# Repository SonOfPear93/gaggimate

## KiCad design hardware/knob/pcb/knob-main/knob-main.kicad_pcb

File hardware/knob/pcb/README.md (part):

## Board A — knob-base

Status: rev 1 layout, generated 2026-11-07 while Ryan was away. ERC/DRC clean, not yet ordered.
Decisions marked **[Claude's call]** are open to change.

Files (`knob-base/`): `knob-base.kicad_sch`, `knob-base.kicad_pcb`, `knob-base.kicad_pro`,
`lib/knob-base.pretty` (SmartKnob hole footprints), `scripts/` (generators), `fab/` (outputs).
The design is fully script-generated; edit the scripts, not the board, or regeneration will undo it:

```sh
PY=/Applications/KiCad/KiCad.app/Contents/Frameworks/Python.framework/Versions/3.9/bin/python3
cd hardware/knob/pcb/knob-base
python3 scripts/gen_sch.py      # schematic
$PY scripts/gen_pcb.py          # placement, hand routes on the flexure, grid router, GND pours (~20 s)
$PY scripts/gen_fab.py          # Gerbers/drill zip, JLC BOM + CPL, renders, schematic PDF, ERC/DRC reports
```

### Credit and what changed from SmartKnob

Derived from **SmartKnob View `electronics/view_base` by Scott Bezek (Apache-2.0)**,
https://github.com/scottbez1/smartknob. Kept, at the same coordinates: the press-sensor flexure
(all inner Edge.Cuts: arc slots r = 15–16 mm, 1.0 mm radial slots either side of four 5 mm arms out to
r = 23.8 mm, the motor-wire cut-out and the Ø3 display-wire hole), MT6701 (U1) at the exact centre on
the front, its 100 n (C20), the four 2512 strain-gauge resistors (R18–R21) on the back of the ±X arms,
the HX711 circuit (U4 + PNP AVDD regulator Q1/R3/R4, excitation filter, 100 Ω/100 n input filter,
decoupling, GNDA–GND net tie NT1), motor holes H1–H3, M2 holes H4–H7 and alignment holes H8/H9.
Hole footprints are copied from SmartKnob's `lib/Holes.pretty`; reference designators match view_base.

Removed: ESP32 module, USB-C, CH340, both regulators, TMC6300, SK6812 LEDs, VEML7700, LCD pads,
test points and the J4/J5 glued-gauge pads. Changed:
- Outline: 81.2 mm rounded square → **Ø75.0 mm circle**, 1.2 mm FR4, 2 layers.
- HX711 group moved onto the rigid quadrant at 135° (back side); power is 3V3 from Board B.
- **[Claude's call]** L1 3.3 µH (C307744, extended, 5k stock) → FB1 ferrite bead GZ2012D101TF (C1015, basic).
  Same 0805 footprint, so C307744 can be fitted instead if the HX711 reading is noisier than SmartKnob's.
- **[Claude's call]** MMBT4403 → SS8550 (C8542, basic; same SOT-23 B-E-C pinout; the HX711 datasheet's own PNP).
- Bridge routing keeps SmartKnob's topology (+X-arm nets cross the inner disc and leave up the 90° arm,
  −X-arm nets leave along the −X arm) but is redrawn for 0.25 mm tracks / 0.15 mm clearance / 0.3 mm edge
  clearance. R18's E+ leaves from the outer root and goes round on the ring. The encoder bus (3V3, CS,
  CLK, DO on F.Cu; GND on B.Cu) now runs down the 270° arm instead of the −X arm.
- Added J1 (JST-SH 8p) and the 3.0 × 7.0 mm wire slot.

### Placement and coordinates

Front view (looking at the knob side), origin at the board centre, +x right, +y up, mm, angles CCW from +x
(alignment holes on the x axis). KiCad file coordinates: board centre at (100, 100), KiCad X = 100 + x,
KiCad Y = 100 − y.

| Item | Position (x, y) | Notes |
|---|---|---|
| Board outline | circle Ø75.0 | 1.2 mm thick |
| U1 MT6701CT (front) | (0, 0) | under the motor magnet, as SmartKnob |
| H1 / H2 / H3 motor (M1.6) | (5.125, −8.877), (−10.25, 0), (5.125, 8.877) | r = 10.25 at −60°/180°/60°, Ø1.7 plated, pad Ø2.4 |
| H4 / H5 / H6 / H7 mount (M2) | (0, −29.8), (−29.8, 0), (0, 29.8), (29.8, 0) | r = 29.8 at 270°/180°/90°/0°, Ø2.2 plated, pad Ø3.5 |
| H8 / H9 alignment | (35, 0), (−35, 0) | r = 35 at 0°/180°, Ø2.2 plated, pad Ø3.5 |
| **Wire slot** | centre (−23.688, −23.688) | r = 33.5 at 225°, 3.0 × 7.0 obround, long axis tangential (along the 135°/315° direction); inner edge r = 32.0, outer r = 35.0; ≥ 8 mm outside the flexure slots, ~4.9 mm from J1's courtyard |
| Display-wire hole (kept) | (−7.071, −7.071) | Ø3.0, r = 10 at 225° |
| Motor-wire cut-out (kept) | centre (8.75, 0) | 3.5 × 7.0, r = 0.75 corners |
| Strain gauges R18/R19/R20/R21 (back) | (23.5, 0), (15.6, 0), (−15.6, 0), (−23.5, 0) | 2512 across the arm roots |
| U4 HX711 (back) | (−15.91, 15.91) | r = 22.5 at 135°, rotated 45°; passives at r ≈ 17–32 |
| **J1 JST-SH (back)** | footprint origin (−10.0, −29.5) | pins 1…8 at y = −31.5, x = −13.5 … −6.5 (front view); cable opening faces the board centre (+y) |

Max part height on the back (towards Board B): J1 2.9 mm (plus the mated plug in front of the opening),
U4 1.75 mm, everything else ≤ 1.3 mm. Front side: only U1 (1.75 mm) and C20, within r ≈ 5 of the centre.

**[Claude's call]** The brief said "HX711 on the rigid ring r ≈ 29–37". The ring between the M2 holes and the
edge is ~7 mm wide and already holds H4–H9, so U4 and its 12 passives sit on the quadrant between the 90° and
180° arms at r ≈ 17–32. That area is rigid: the radial flexure slots stop at r = 23.8, so each quadrant is joined to
the outer ring along its full width (SmartKnob put LEDs and caps there).

### Connector J1 to Board B

JST SM08B-SRSS-TB (side entry, 1.0 mm), back side. Board B uses the same header (C160407), so the cable is a
JST-SH 8-way **pin-1-to-pin-1** (same-side) lead, e.g. two SHR-08V-S housings with SSH crimps or a pre-made
"Qwiic-style" 8-way cable.

| Pin | Net | Board A use |
|---|---|---|
| 1 | 3V3 | MT6701 VDD/MODE, HX711 VSUP/DVDD/RATE, PNP emitter |
| 2 | GND | |
| 3 | ENC_CS | MT6701 pin 8 (CSN) |
| 4 | ENC_CLK | MT6701 pin 7 (CLK) |
| 5 | ENC_DO | MT6701 pin 6 (DO) |
| 6 | HX_SCK | HX711 PD_SCK |
| 7 | HX_DOUT | HX711 DOUT |
| 8 | GND | |

MT6701 MODE is tied to VDD (SSI, as SmartKnob). HX711 RATE is tied high (80 SPS), XI to AGND (internal
oscillator). Board A has no pull-ups or series resistors on the interface; SmartKnob had 2.2 k pull-ups on the
encoder DO/CLK on its main board, so put those on Board B if the SSI read needs them.

### Parts (JLC, qty 5 boards)

Stock and price from the local kicad-jlcpcb-tools parts DB (snapshot dated 2026-09-21; not refreshed today,
that needs a download). Unit price is the JLC tier for the quantity bought.

| Ref | Value | MPN | LCSC | Type | Stock | Unit | Qty (5 bds) | Cost |
|---|---|---|---|---|---|---|---|---|
| U1 | MT6701CT-STD-R | Novosense MT6701CT-STD-R | C3003196 | Extended | 5,421 | $1.724 | 5 | $8.62 |
| U4 | HX711 | Avia HX711 | C6705483 | Extended | 177,864 | $0.505 | 5 | $2.52 |
| J1 | JST-SH 8p | JST SM08B-SRSS-TB(LF)(SN) | C160407 | Extended | 125,076 | $0.332 | 5 | $1.66 |
| R18–R21 | 330 Ω 2512 (strain) | Uniroyal 25121WJ0331T4E | C19866 | Extended | 113,348 | $0.028 | 20 | $0.56 |
| Q1 | SS8550 | CJ SS8550 Y2 | C8542 | Basic | 888,952 | $0.015 | 5 | $0.07 |
| FB1 | 100 Ω@100 MHz 0805 | Sunlord GZ2012D101TF | C1015 | Basic | 2,395,344 | $0.027 | 5 | $0.14 |
| C16, C18 | 10 µF 0805 | Samsung CL21A106KAYNNNE | C15850 | Basic | 5,982,699 | $0.084 | 10 | $0.84 |
| C12, C19, C20, C22, C23 | 100 nF 0603 | Yageo CC0603KRX7R9BB104 | C14663 | Basic | 53,676,678 | $0.012 | 25 | $0.30 |
| R3 | 10 k 0603 | Uniroyal 0603WAF1002T5E | C25804 | Basic | 24,484,378 | $0.003 | 5 | $0.01 |
| R4 | 8.2 k 0603 | Uniroyal 0603WAF8201T5E | C25981 | Basic | 1,133,039 | $0.004 | 5 | $0.02 |
| R5, R6 | 100 Ω 0603 | Uniroyal 0603WAF1000T5E | C22775 | Basic | 12,954,942 | $0.003 | 10 | $0.03 |
| NT1 | net tie | copper only | — | not placed | | | | |

BOM cost for 5 boards: **components ≈ $14.78**, plus 4 extended-part fees (≈ $3 each) ≈ **$26.80**. Not included:
bare PCBs (Ø75, 1.2 mm, 2 layers), PCBA setup for **both sides** (U1/C20 front, the rest back), stencil, shipping.
No JLC quote was requested. Every line is ≥ 10× the build quantity; the tightest is the MT6701 (5.4k).

### Fab outputs (`knob-base/fab/`)

- `knob-base-gerbers.zip`: Gerbers (F/B Cu, Mask, Paste, Silkscreen, Edge.Cuts) + Excellon drills (PTH; the NPTH file is empty).
- `knob-base-BOM-JLC.csv`, `knob-base-CPL-JLC.csv`: JLC format. CPL rotation uses kicad-jlcpcb-tools' rule (back side
  `180 − rot`) plus its corrections (SOIC +270, SOT-23 −90) and +180 for the JST SH header (by analogy with the
  plugin's JST_GH_SM/JST_PH_S entries; Board B uses the same value).
- `knob-base-top.png`, `knob-base-bottom.png` (`kicad-cli pcb render`), `knob-base-schematic.pdf`, `erc-report.txt`, `drc-report.txt`.
- Order settings: 1.2 mm thickness (the flexure depends on it), 2 layers, any mask colour.

### Verification

```sh
kicad-cli sch erc knob-base.kicad_sch                                     # 0 errors, 0 warnings
kicad-cli pcb drc --schematic-parity --severity-all knob-base.kicad_pcb   # 0 violations, 0 unconnected, 0 parity issues
```

Rules in `knob-base.kicad_pro`: clearance 0.15 mm (pours 0.25), all tracks 0.25 mm, vias 0.6/0.3 mm, copper to edge
0.3 mm, min drill 0.3 mm. Routing: the flexure/arm traces are hand-placed in `gen_pcb.py`; everything outside the
flexure is routed by `scripts/router.py` (a small 2-layer grid maze router, kept away from the arms, the inner disc and
the M2 screw/nut and alignment-pin areas), giving 163 track segments and 28 vias. GND is poured on both layers.

### Risks / open points (Board A)

1. **Board B's 225° mounting hole (r = 33) sits directly under this wire slot (r = 33.5, 225°).** The 16 wires
   will drop onto B's screw/standoff. Move one of them (for example B's hole to 210°/240°, or the slot) before ordering.
   Board B's 135° hole (r = 33) also lands near A's back-side HX711 passives (R5/R6 reach r ≈ 32.5): a standoff there needs
   to be ≤ Ø2 mm wide at A, or the hole moved.
2. Flexure geometry is SmartKnob's, but the clamp ring is now round, and the quadrants carry the HX711 group.
   Press sensitivity and stiffness are untested.
3. Two-sided assembly (U1 and C20 front, everything else back), as SmartKnob's strain gauges were already on the back.
   JLC charges a second side; the economic PCBA service may not cover it.
4. CPL rotations for J1 (+180, guessed), Q1 and the SOICs must be checked in JLC's placement preview.
5. J1 is a side-entry header with its opening facing the centre. The mated plug lies over bare tracks towards
   r ≈ 23 and needs ~5 mm of space in front of the opening plus ~3 mm height. Board B parts below it must clear
   that (A–B gap target 8 mm).
6. Strain signals: S+ and E+ have longer runs than SmartKnob (the HX711 moved further from the +X arm), and some
   of the outer routing uses vias. The 100 Ω/100 nF input filter, separate GNDA (net tie at the HX711) and GND pours
   on both sides should hold the noise down, but this is unproven. FB1 vs the original 3.3 µH is a second variable.
7. The flexure slots are 1.0 mm wide, at JLC's minimum milled-slot width (unchanged from SmartKnob).
8. Parts DB snapshot is ~7 weeks old. Re-check MT6701 (C3003196) stock before ordering.

## Board B — knob-main

Status: rev 1 layout, generated 2026-11-07 while Ryan was away. Not yet ordered. Decisions marked
**[Claude's call]** are open to change. Verification results are in the "Verification" subsection below.

Files (`knob-main/`): `knob-main.kicad_sch/.kicad_pcb/.kicad_pro`, `knob-main.kicad_sym` (local symbol: AP7361C-33ER), `knob-main.pretty/` (local footprints:
ESP32-S3-WROOM-1 copy with 0.3 mm EP vias, 13-pad wire field, motor pads), `gen/` (generators), `fab/` (outputs).
Everything is script-generated; edit the scripts, not the board:

```sh
PY=/Applications/KiCad/KiCad.app/Contents/Frameworks/Python.framework/Versions/3.9/bin/python3
K=/Applications/KiCad/KiCad.app/Contents/MacOS/kicad-cli
cd hardware/knob/pcb/knob-main
python3 gen/make_footprints.py && python3 gen/build_sch.py           # local footprints, schematic + .kicad_pro
$K sch upgrade knob-main.kicad_sch && $K sch export netlist -o /tmp/b.net knob-main.kicad_sch
$PY gen/build_pcb.py /tmp/b.net knob-main.kicad_pcb && python3 gen/build_sch.py --pro-only
$PY gen/prefan.py knob-main.kicad_pcb    # hand routes at the DRV8311 + GND/3V3 fan-out vias to the inner planes
$PY gen/dsn.py knob-main.kicad_pcb /tmp/b.dsn                         # then Freerouting 1.9.0 (Java 21):
java -jar freerouting-1.9.0.jar -de /tmp/b.dsn -do /tmp/b.ses -mp 30 -inc Plane
$PY gen/ses.py knob-main.kicad_pcb /tmp/b.ses                         # 0 unrouted in this revision
$PY gen/finish_pcb.py knob-main.kicad_pcb   # cleanup, pours, stitching vias
$PY gen/fab.py knob-main.kicad_pcb fab      # gerbers/drill zip, JLC BOM/CPL, renders
```

(`gen/inner_route.py` and `dsn.py --in2-signal` exist for finishing leftovers on In2 but were not needed here.
`build_pcb.py` calls `pcbnew.SaveBoard`, which rewrites the .kicad_pro with defaults, hence the
`--pro-only` re-run that restores the net classes. Freerouting 2.x needs Java 25 and routed this board badly;
1.9.0 is used.)

### What is on it

| Block | Parts | Notes |
|---|---|---|
| MCU | U1 ESP32-S3-WROOM-1-N16R8 | GPIO map exactly as the design doc §5 table (no changes). EN: 10k/1µF RC + RESET button SW1. GPIO0: 10k pull-up + BOOT button SW2. Status LED D3 (red) + 1k on GPIO48. 10µF + 100nF at the 3V3 pin. |
| USB | J1 USB-C 16P (HRO TYPE-C-31-M-12), U2 USBLC6-2SC6, R1/R2 5.1k CC pull-downs | D+/D− direct to GPIO20/19, VBUS also clamped by U2. SBU unused. |
| 5 V in | J2 JST-XH B4B-XH-A (THT, **bottom side**), D1/D2 SS34 Schottky OR, C1 22µF | J2 pinout = GaggiMate controller J4 (the display connector): 1 +5V, 2 controller UART_TX0, 3 controller UART_RX0, 4 GND. Only 1/4 are used; 2/3 go to test pads TP6/TP7. +5V after the diodes ≈ 4.5–4.6 V. |
| 3.3 V | U3 AP7361C-33ER-13 (Diodes, SOT-223R, 1 A, 340 mV dropout @ 1 A), C2 10µF/25V in, C3 22µF + C4 100nF out | Datasheet asks CIN ≥ 1 µF, COUT ≥ 2.2 µF ceramic. Tab (= OUT on the "R" pinout) on a top-copper +3V3 island with vias into the In2 +3V3 plane. See the U3 note below. |
| Panel power | Q1 AO3401A high-side P-FET, Q2 2N7002, R14 100k, C8 100nF, R15 10k, R16 100k, C9 10µF | LCD_EN (GPIO17) high = panel on. Gate RC gives ≈1 ms soft start so the panel's input caps don't sag the 3V3 rail. Default off (R16 pull-down). |
| Display/touch | R6–R11 33Ω series on QSPI CS/CLK/D0–D3 (at the ESP32), R12/R13 4.7k touch I2C pull-ups **to 3V3_LCD** | Pull-ups go to the switched rail so nothing back-powers the touch IC when the panel is off. **[Claude's call]** the 33Ω resistors damp ringing on the ~10–15 cm loose wire bundle. |
| Motor | U4 DRV8311HRRWR, J5 Molex PicoBlade 53261-0371, J6 3 bare pads | See "DRV8311H configuration". |
| Board A link | J8 JST-SH SM08B-SRSS-TB, R21–R23 2.2k pull-ups on ENC_CS/ENC_CLK/ENC_DO | Board A has no pull-ups; SmartKnob used 2.2k. |
| Wire pads | J7 13 bare THT pads (2 staggered rows, 2.0 mm pitch, Ø0.9 drill) | Screen bundle, same numbering as board C J2. |
| Test pads | TP1 +5V, TP2 +3V3, TP3 GND, TP4 U0TXD, TP5 U0RXD, TP6/TP7 XH pins 2/3 | Ø1.5 mm SMD pads. |

### DRV8311H configuration (hardware variant)

- **MODE tied to AVDD → 3x PWM mode** (datasheet Table 8-2; this setting also selects the 5 A OCP level).
  INHA/INHB/INHC = GPIO4/GPIO5/GPIO18 PWM. All three INLx are tied together to **DRV_EN (GPIO47, 100k pull-down)**:
  INLx = 0 puts every half-bridge in Hi-Z (Table 8-4), so the motor is free while the ESP32 boots.
- nSLEEP = GPIO21 with 100k pull-down. nFAULT → GPIO3 with 10k pull-up to 3V3.
- **GAIN left open (Hi-Z) → 1 V/A** current-sense gain, ±1.65 A full scale around CSAREF/2. SOA/SOB → GPIO1/GPIO2 (ADC1); SOC unused.
  **[Claude's call]**: the gimbal motor draws well under 1 A at 5 V, so 1 V/A uses the ADC range without clipping.
- **SLEW: 47k to GND → 75 V/µs** (and the matching dead time). **[Claude's call]**: slow enough for low EMI near the
  QSPI bundle, fast enough for 20–30 kHz FOC PWM.
- CSAREF tied to AVDD with 100nF; AVDD 1µF; CP–VM 100nF/50V; VM 100nF/50V + 2× 22µF/25V; VIN_AVDD (from +5V) 100nF + 10µF/25V.
- The exposed pad has 4 × 0.3 mm vias to the In1 GND plane. PGND/AGND pins are tied straight into the pad.

### Placement and coordinates

Front view (looking at the knob; board B's top side faces board A and the front), origin at the board centre,
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
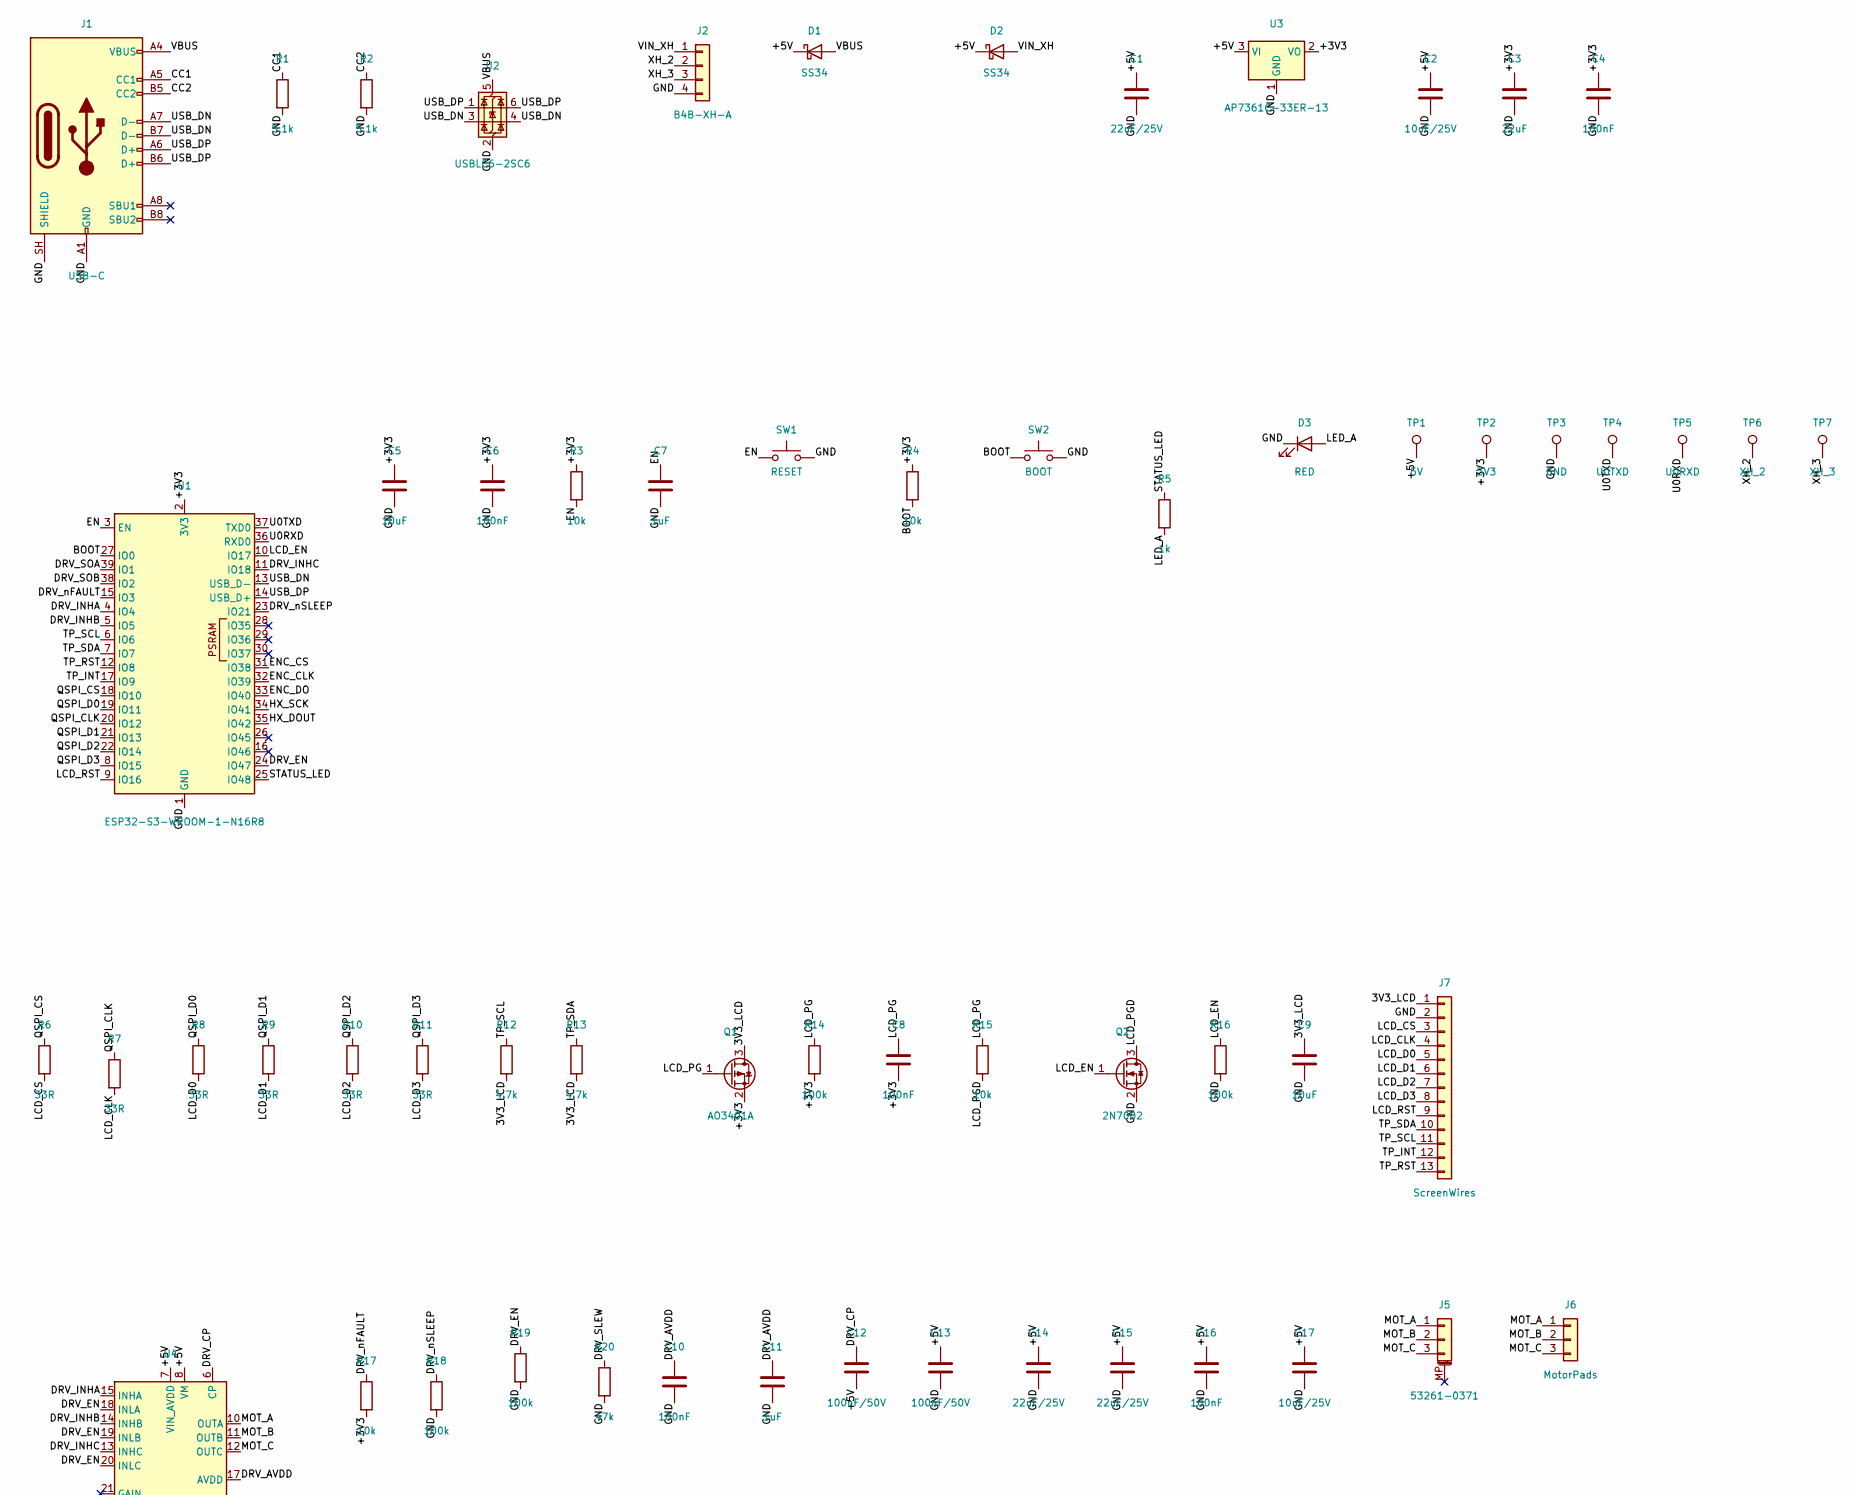
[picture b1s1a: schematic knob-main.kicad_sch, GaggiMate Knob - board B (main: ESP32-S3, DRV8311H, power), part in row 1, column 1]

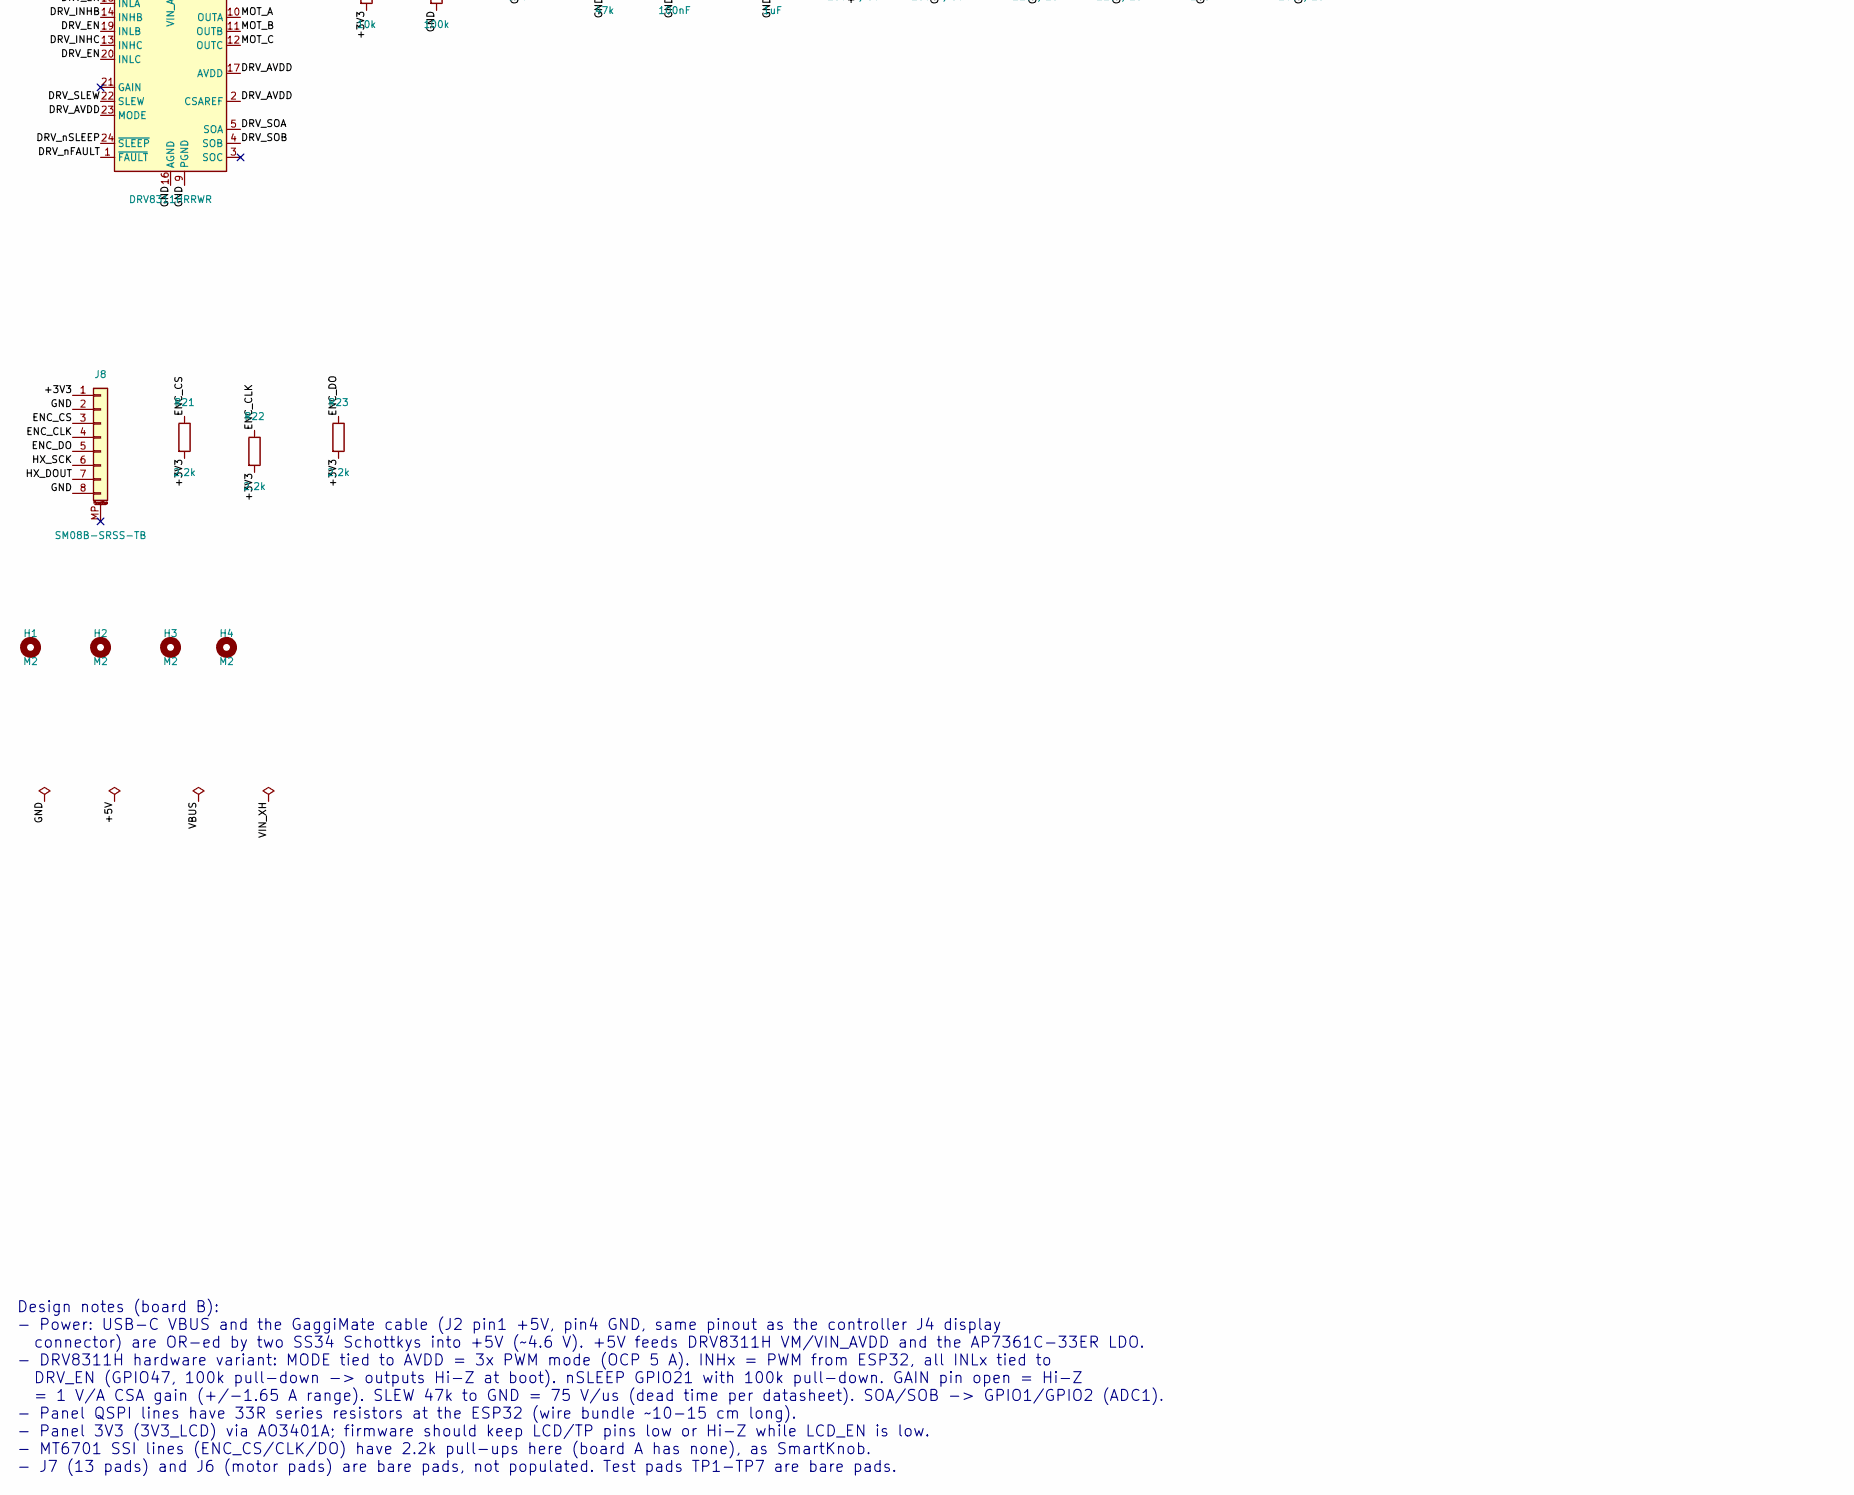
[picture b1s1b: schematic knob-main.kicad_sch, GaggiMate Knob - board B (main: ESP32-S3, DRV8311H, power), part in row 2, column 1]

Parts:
C1, C14, C15: 22uF/25V; C_1206_3216Metric; MPN CL31A226KAHNNNE; LCSC C12891
C2, C17: 10uF/25V; C_0805_2012Metric; MPN CL21A106KAYNNNE; LCSC C15850
C3: 22uF; C_0805_2012Metric; MPN CL21A226MAQNNNE; LCSC C45783
C4, C6, C8, C10, C16: 100nF; C_0402_1005Metric; MPN CL05B104KO5NNNC; LCSC C1525
C5, C9: 10uF; C_0603_1608Metric; MPN CL10A106KP8NNNC; LCSC C19702
C7, C11: 1uF; C_0402_1005Metric; MPN CL05A105KA5NQNC; LCSC C52923
C12, C13: 100nF/50V; C_0603_1608Metric; MPN CC0603KRX7R9BB104; LCSC C14663
D1, D2: SS34; D_SMA; MPN SS34; LCSC C8678
D3: RED; LED_0603_1608Metric; MPN KT-0603R; LCSC C2286
H1, H2, H3, H4: M2; MountingHole_2.2mm_M2
J1: USB-C; USB_C_Receptacle_HRO_TYPE-C-31-M-12; MPN TYPE-C-31-M-12; LCSC C165948
J2: B4B-XH-A; JST_XH_B4B-XH-A_1x04_P2.50mm_Vertical; MPN B4B-XH-A(LF)(SN); LCSC C144395
J5: 53261-0371; Molex_PicoBlade_53261-0371_1x03-1MP_P1.25mm_Horizontal; MPN 532610371; LCSC C293630
J6: MotorPads; MotorPads_3_P2.54mm
J7: ScreenWires; WirePads_13_2Rows_P2.0mm
J8: SM08B-SRSS-TB; JST_SH_SM08B-SRSS-TB_1x08-1MP_P1.00mm_Horizontal; MPN SM08B-SRSS-TB(LF)(SN); LCSC C160407
Q1: AO3401A; SOT-23; MPN AO3401A; LCSC C15127
Q2: 2N7002; SOT-23; MPN 2N7002; LCSC C8545
R1, R2: 5.1k; R_0402_1005Metric; MPN 0402WGF5101TCE; LCSC C25905
R3, R4, R15, R17: 10k; R_0402_1005Metric; MPN 0402WGF1002TCE; LCSC C25744
R5: 1k; R_0402_1005Metric; MPN 0402WGF1001TCE; LCSC C11702
R6, R7, R8, R9, R10, R11: 33R; R_0402_1005Metric; MPN 0402WGF330JTCE; LCSC C25105
R12, R13: 4.7k; R_0402_1005Metric; MPN 0402WGF4701TCE; LCSC C25900
R14, R16, R18, R19: 100k; R_0402_1005Metric; MPN 0402WGF1003TCE; LCSC C25741
R20: 47k; R_0402_1005Metric; MPN 0402WGF4702TCE; LCSC C25792
R21, R22, R23: 2.2k; R_0402_1005Metric; MPN 0402WGF2201TCE; LCSC C25879
SW1: RESET; SW_Push_1P1T_XKB_TS-1187A; MPN TS-1187A-B-A-B; LCSC C318884
SW2: BOOT; SW_Push_1P1T_XKB_TS-1187A; MPN TS-1187A-B-A-B; LCSC C318884
TP1: 5V; TestPoint_Pad_D1.5mm
TP2: 3V3; TestPoint_Pad_D1.5mm
TP3: GND; TestPoint_Pad_D1.5mm
TP4: U0TXD; TestPoint_Pad_D1.5mm
TP5: U0RXD; TestPoint_Pad_D1.5mm
TP6: XH_2; TestPoint_Pad_D1.5mm
TP7: XH_3; TestPoint_Pad_D1.5mm
U1: ESP32-S3-WROOM-1-N16R8; ESP32-S3-WROOM-1_EPvia0.3; MPN ESP32-S3-WROOM-1-N16R8; LCSC C2913202
U2: USBLC6-2SC6; SOT-23-6; MPN USBLC6-2SC6; LCSC C2687116
U3: AP7361C-33ER-13; SOT-223-3_TabPin2; MPN AP7361C-33ER-13; LCSC C3743528
U4: DRV8311HRRWR; Texas_RRW0024A_WQFN-24-1EP_3x3mm_P0.4mm_EP1.9x1.9mm; MPN DRV8311HRRWR; LCSC C5218862

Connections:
/3V3_LCD: C9.1, J7.1, Q1.3 (D), R12.2, R13.2
/+3V3: C3.1, C4.1, C5.1, C6.1, C8.2, J8.1, Q1.2 (S), R3.1, R4.1, R14.2, R17.2, R21.2, R22.2, R23.2, TP2.1, U1.2 (3V3), U3.2 (VO)
/+5V: C1.1, C2.1, C12.2, C13.1, C14.1, C15.1, C16.1, C17.1, D1.1 (K), D2.1 (K), TP1.1, U3.3 (VI), U4.7 (VIN_AVDD), U4.8 (VM)
/BOOT: R4.2, SW2.1, U1.27 (IO0)
/CC1: J1.A5 (CC1), R1.1
/CC2: J1.B5 (CC2), R2.1
/DRV_AVDD: C10.1, C11.1, U4.2 (CSAREF), U4.17 (AVDD), U4.23 (MODE)
/DRV_CP: C12.1, U4.6 (CP)
/DRV_EN: R19.1, U1.24 (IO47), U4.18 (INLA), U4.19 (INLB), U4.20 (INLC)
/DRV_INHA: U1.4 (IO4), U4.15 (INHA)
/DRV_INHB: U1.5 (IO5), U4.14 (INHB)
/DRV_INHC: U1.11 (IO18), U4.13 (INHC)
/DRV_SLEW: R20.1, U4.22 (SLEW)
/DRV_SOA: U1.39 (IO1), U4.5 (SOA)
/DRV_SOB: U1.38 (IO2), U4.4 (SOB)
/DRV_nFAULT: R17.1, U1.15 (IO3), U4.1 (~FAULT)
/DRV_nSLEEP: R18.1, U1.23 (IO21), U4.24 (~SLEEP)
/EN: C7.1, R3.2, SW1.1, U1.3 (EN)
/ENC_CLK: J8.4, R22.1, U1.32 (IO39)
/ENC_CS: J8.3, R21.1, U1.31 (IO38)
/ENC_DO: J8.5, R23.1, U1.33 (IO40)
/GND: C1.2, C2.2, C3.2, C4.2, C5.2, C6.2, C7.2, C9.2, C10.2, C11.2, C13.2, C14.2, C15.2, C16.2, C17.2, D3.1 (K), J1.A1 (GND), J1.A12 (GND), J1.B1 (GND), J1.B12 (GND), J1.SH (SHIELD), J2.4, J7.2, J8.2, J8.8, Q2.2 (S), R1.2, R2.2, R16.2, R18.2, R19.2, R20.2, SW1.2, SW2.2, TP3.1, U1.1 (GND), U1.40 (GND), U1.41 (GND), U2.2 (GND), U3.1 (GND), U4.9 (PGND), U4.16 (AGND), U4.25 (PGND)
/HX_DOUT: J8.7, U1.35 (IO42)
/HX_SCK: J8.6, U1.34 (IO41)
/LCD_CLK: J7.4, R7.2
/LCD_CS: J7.3, R6.2
/LCD_D0: J7.5, R8.2
/LCD_D1: J7.6, R9.2
/LCD_D2: J7.7, R10.2
/LCD_D3: J7.8, R11.2
/LCD_EN: Q2.1 (G), R16.1, U1.10 (IO17)
/LCD_PG: C8.1, Q1.1 (G), R14.1, R15.1
/LCD_PGD: Q2.3 (D), R15.2
/LCD_RST: J7.9, U1.9 (IO16)
/LED_A: D3.2 (A), R5.2
/MOT_A: J5.1, J6.1, U4.10 (OUTA)
/MOT_B: J5.2, J6.2, U4.11 (OUTB)
/MOT_C: J5.3, J6.3, U4.12 (OUTC)
/QSPI_CLK: R7.1, U1.20 (IO12)
/QSPI_CS: R6.1, U1.18 (IO10)
/QSPI_D0: R8.1, U1.19 (IO11)
/QSPI_D1: R9.1, U1.21 (IO13)
/QSPI_D2: R10.1, U1.22 (IO14)
/QSPI_D3: R11.1, U1.8 (IO15)
/STATUS_LED: R5.1, U1.25 (IO48)
/TP_INT: J7.12, U1.17 (IO9)
/TP_RST: J7.13, U1.12 (IO8)
/TP_SCL: J7.11, R12.1, U1.6 (IO6)
/TP_SDA: J7.10, R13.1, U1.7 (IO7)
/U0RXD: TP5.1, U1.36 (RXD0)
/U0TXD: TP4.1, U1.37 (TXD0)
/USB_DN: J1.A7 (D-), J1.B7 (D-), U1.13 (USB_D-), U2.3 (I/O2), U2.4 (I/O2)
/USB_DP: J1.A6 (D+), J1.B6 (D+), U1.14 (USB_D+), U2.1 (I/O1), U2.6 (I/O1)
/VBUS: D1.2 (A), J1.A4 (VBUS), J1.A9 (VBUS), J1.B4 (VBUS), J1.B9 (VBUS), U2.5 (VBUS)
/VIN_XH: D2.2 (A), J2.1
/XH_2: J2.2, TP6.1
/XH_3: J2.3, TP7.1

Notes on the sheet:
Design notes (board B): - Power: USB-C VBUS and the GaggiMate cable (J2 pin1 +5V, pin4 GND, same pinout as the controller J4 display connector) are OR-ed by two SS34 Schottkys into +5V (~4.6 V). +5V feeds DRV8311H VM/VIN_AVDD and the AP7361C-33ER LDO. - DRV8311H hardware variant: MODE tied to AVDD 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

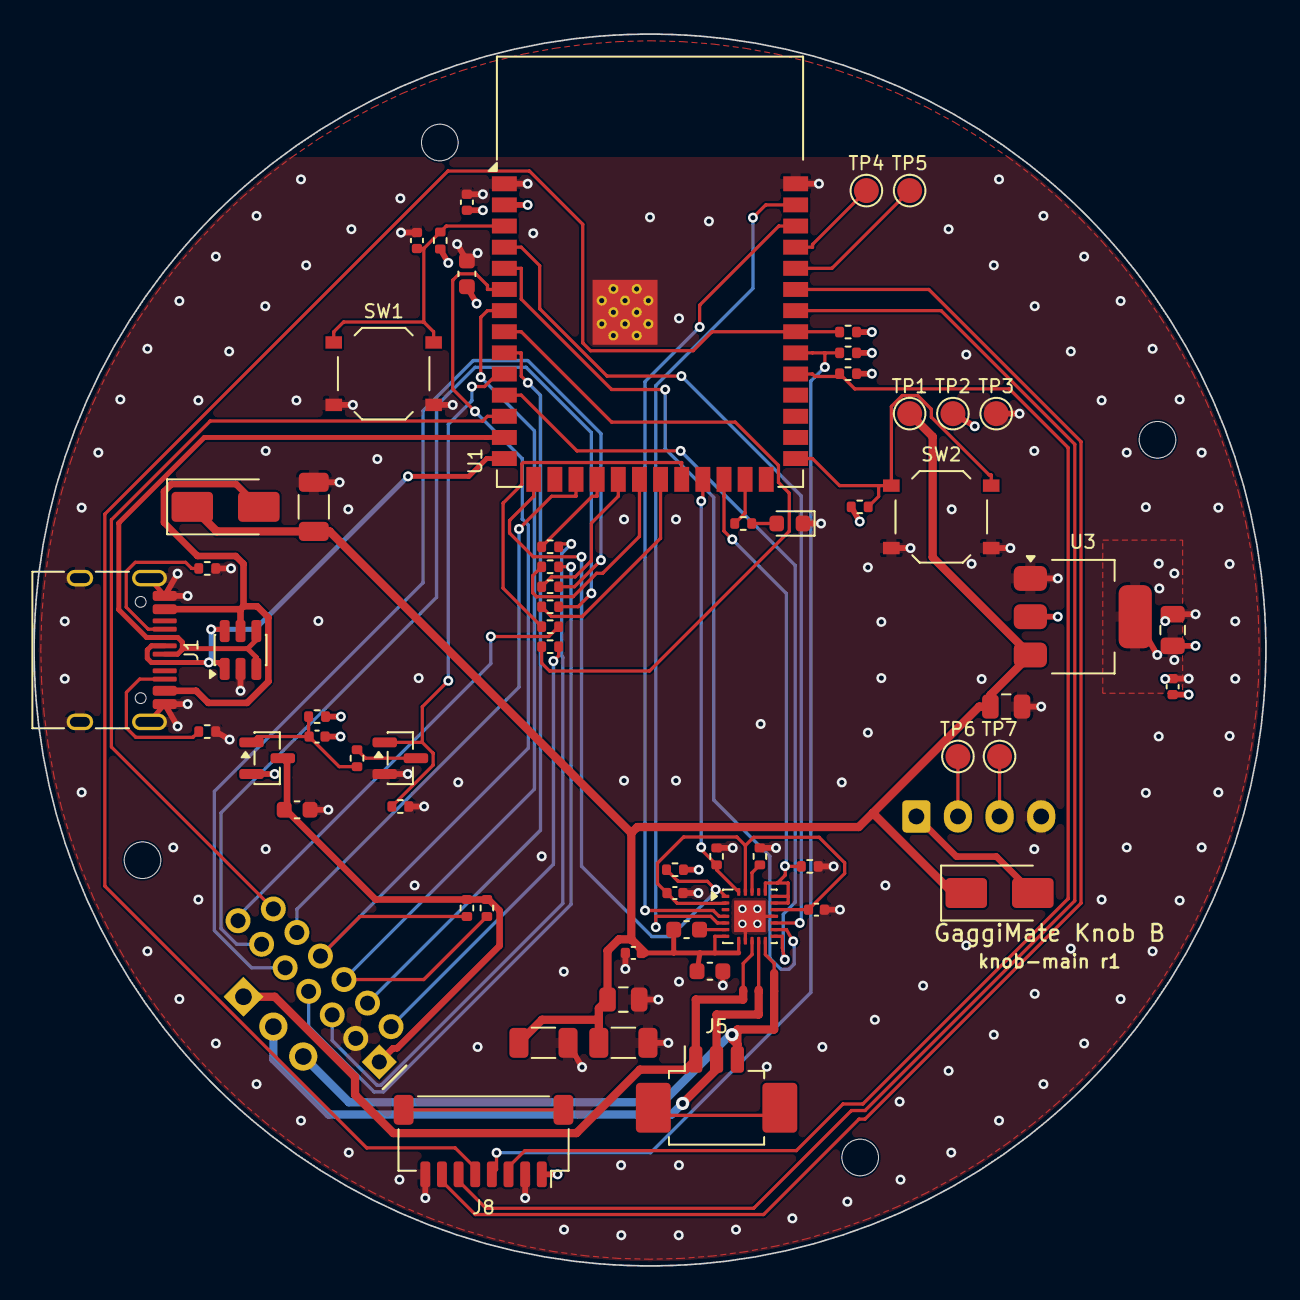
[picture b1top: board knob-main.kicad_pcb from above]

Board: 4 copper layers, 74.0 x 74.0 mm, 68 parts (1 on the bottom side), 57 nets.

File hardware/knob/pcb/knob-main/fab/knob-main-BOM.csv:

Comment,Designator,Footprint,LCSC
22uF/25V,"C1,C14,C15",C_1206_3216Metric,C12891
100nF/50V,"C12,C13",C_0603_1608Metric,C14663
10uF/25V,"C2,C17",C_0805_2012Metric,C15850
22uF,C3,C_0805_2012Metric,C45783
100nF,"C4,C6,C8,C10,C16",C_0402_1005Metric,C1525
10uF,"C5,C9",C_0603_1608Metric,C19702
1uF,"C7,C11",C_0402_1005Metric,C52923
SS34,"D1,D2",D_SMA,C8678
RED,D3,LED_0603_1608Metric,C2286
USB-C,J1,USB_C_Receptacle_HRO_TYPE-C-31-M-12,C165948
B4B-XH-A,J2,JST_XH_B4B-XH-A_1x04_P2.50mm_Vertical,C144395
53261-0371,J5,Molex_PicoBlade_53261-0371_1x03-1MP_P1.25mm_Horizontal,C293630
SM08B-SRSS-TB,J8,JST_SH_SM08B-SRSS-TB_1x08-1MP_P1.00mm_Horizontal,C160407
AO3401A,Q1,SOT-23,C15127
2N7002,Q2,SOT-23,C8545
5.1k,"R1,R2",R_0402_1005Metric,C25905
4.7k,"R12,R13",R_0402_1005Metric,C25900
100k,"R14,R16,R18,R19",R_0402_1005Metric,C25741
47k,R20,R_0402_1005Metric,C25792
2.2k,"R21,R22,R23",R_0402_1005Metric,C25879
10k,"R3,R4,R15,R17",R_0402_1005Metric,C25744
1k,R5,R_0402_1005Metric,C11702
33R,"R6,R7,R8,R9,R10,R11",R_0402_1005Metric,C25105
RESET,SW1,SW_Push_1P1T_XKB_TS-1187A,C318884
BOOT,SW2,SW_Push_1P1T_XKB_TS-1187A,C318884
ESP32-S3-WROOM-1-N16R8,U1,ESP32-S3-WROOM-1_EPvia0.3,C2913202
USBLC6-2SC6,U2,SOT-23-6,C2687116
AP7361C-33ER-13,U3,SOT-223-3_TabPin2,C3743528
DRV8311HRRWR,U4,Texas_RRW0024A_WQFN-24-1EP_3x3mm_P0.4mm_EP1.9x1.9mm,C5218862

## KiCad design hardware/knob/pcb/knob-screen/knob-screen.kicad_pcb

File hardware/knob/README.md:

# GaggiMate Knob — hardware (rev 1)

A SmartKnob-style motorised haptic knob that replaces GaggiMate's round touchscreen
unit on a Gaggia Classic / Classic Pro. Design: [`docs/superpowers/specs/2026-11-07-smartknob-input-design.md`](../../docs/superpowers/specs/2026-11-07-smartknob-input-design.md).
Firmware: [`docs/knob-firmware.md`](../../docs/knob-firmware.md) (`pio run -e display-knob`).

**Status: rev 1 is designed but not built.** Every file passes its automated checks
(KiCad ERC/DRC, CAD interference check, firmware builds and unit tests), but nothing has
been fabricated, printed, assembled or powered. Expect a rev 2.

| Folder | What |
|---|---|
| [`pcb/knob-base`](pcb/knob-base) | Board A: Ø75 mm, 1.2 mm flexure board (press sensing), MT6701 encoder, HX711 |
| [`pcb/knob-main`](pcb/knob-main) | Board B: Ø74 mm, 4-layer main board, ESP32-S3, DRV8311H motor driver, power, USB-C |
| [`pcb/knob-screen`](pcb/knob-screen) | Board C: Ø46 mm adapter behind the 1.75" AMOLED (31-pin FPC) |
| [`pcb/README.md`](pcb/README.md) | Per-board details: parts + stock, pinouts, coordinates, risks |
| [`mechanical`](mechanical) | Printed parts (build123d → STEP/STL), renders, interference check, hardware list |

## What to buy

| Item | Notes |
|---|---|
| 3 PCB orders at JLCPCB (below) | Gerbers, BOM and CPL are in each board's `fab/` folder |
| 1.75" round AMOLED, 466×466, CO5300 + CST9217 touch, 31-pin 0.3 mm FPC | Guaranteed match: buy Waveshare's ESP32-S3-Touch-AMOLED-1.75 board (~US$45–68) and unclip its panel. A bare AliExpress panel only if its FPC pinout matches the table in the design doc |
| SparkFun ROB-20441 motor | You already have these |
| Screws, heat-set inserts, tape, wire | See [`mechanical/README.md`](mechanical/README.md#hardware): mostly M2, one M3 thumbscrew, 13 × 30 AWG wire |
| JST-SH 8-pin cable (~50 mm, same-end/pin-1-to-pin-1) | Board A ↔ board B |
| Filament | PETG or ASA (the top of the machine gets warm) |

## JLCPCB ordering notes and price estimate (5 of each board)

Bare-board prices are from JLCPCB's online quote today (7 Nov 2026), entered by size and
spec only (no files uploaded, nothing ordered). Assembly is calculated from JLCPCB's
published fees (Economic PCBA: $8.18 setup, $1.53 stencil, $3.07 per extended part)
plus the parts cost from each BOM. Treat it as ±25 %: the real number appears once the
Gerber/BOM/CPL are uploaded.

| Board | PCB spec | Bare (5) | Assembly + parts (5) | Est. total |
|---|---|---|---|---|
| A knob-base | 2-layer, 75×75, **1.2 mm**, HASL | $4 | ~$25 (bottom side only, see below) | **~$29** |
| B knob-main | 4-layer, 74×74, 1.6 mm, standard 3–4 day build | $8 | ~$86 (8 extended parts; J2 is through-hole: add JLC hand-soldering or fit it yourself) | **~$94** |
| C knob-screen | 2-layer, 46×46, 1.0 mm, **tented vias** | $4 | ~$14 | **~$18** |
| | | | Shipping (UPS, one combined order) | ~$27 |
| | | | **Total for 5 units** | **≈ $170 (≈ $34/unit)** |

Plus the panel (~$45–68 each), which costs more than all the electronics put together.

Watch for:
- **Board A has parts on both sides.** Only the MT6701 (U1, SOIC-8) and its capacitor
  (C20) are on the front. Cheapest: order Economic assembly of the **bottom side only**
  and hand-solder U1 + C20 (easy SOIC-8 / 0603). Full double-sided Standard assembly
  works too but costs about $75 more ($51 setup + $16 stencil).
- **Board C quote defaulted to a paid via-covering option** at 1.0 mm. Pick "Tented".
- **Board B quote defaulted to an expedited build time** for 4 layers. Pick the
  standard 3–4 day option ($0).
- In JLCPCB's placement preview, check rotations on: board B U1 (ESP32), U4
  (DRV8311H), J5/J8 (JST connectors), U3; board A J1, Q1, U4; board C J1 (FPC). The
  CPLs include a best guess for each.
- Stock was checked live today for the key parts: ESP32-S3-WROOM-1-N16R8 28k,
  DRV8311HRRWR 8.5k, FH26W-31S 9.6k, AP7361C-33ER-13 1.5k (backup: LDL1117S33R). The
  lowest-stock part on board A is the MT6701 (~5k in Sept); recheck before ordering.

## Build order (suggested)

1. Print the parts (see mechanical README for orientation and settings) and fit-check
   them against each other and on the machine's housing edge before soldering anything.
2. Board B alone on USB-C: check 3V3, flash `display-knob`, confirm USB serial logs.
3. Board C + panel on short wires to board B on the bench: confirm the display
   (orientation/offset may need a tweak in `GAGGIMATE_KNOB_AMOLED_175_HW_CONFIG`).
4. Board A + motor + MountBase, cabled to B: first boot runs motor calibration
   (the knob turns by itself briefly). Then hold BOOT 2–6 s for press calibration.
5. Thread the 13 screen wires down the MountBase tube, out through the 225° channel and
   board A's slot, onto board B's pads. Close up, mount on the machine, tighten the
   clamp.

## Top risks for rev 1

1. **Panel pinout/orientation:** follows Waveshare's schematic and 3D model; board C's
   connector position is good to ±1 mm.
2. **Press sensing:** the flexure is SmartKnob's, but the outline is round and it is
   clamped only at 4 screws. Sensitivity/noise need checking on hardware.
3. **Haptic feel:** the Ø66 knob ring has ~1.9× the inertia of SmartKnob's knob, and
   detent strengths are starting values.
4. **Thin parts of the case:** 1.55 mm wall around board A; the groove overhang needs a
   clean print.
5. **Depth:** ~61 mm vs ~37 mm for the stock unit, giving more lever on the groove when the
   knob is pressed. The thumbscrew clamp is meant to handle that, but it is untested.
6. **USB-C faces down** (toward the machine, in front of the housing edge) because
   the stack is rotated to keep the ESP32 antenna off the steel. Firmware also updates
   over Wi-Fi like stock GaggiMate.

## Credits and licences

Flexure, strain-gauge and encoder circuit, motor interface, RotorSpacer and parts of
the firmware come from [SmartKnob](https://github.com/scottbez1/smartknob) by Scott Bezek
(Apache-2.0 software/electronics, CC-BY-4.0 mechanical). GaggiMate is CC BY-NC-SA 4.0;
the housing groove profile comes from GaggiMate's case files. Panel pinout from
Waveshare's published ESP32-S3-Touch-AMOLED-1.75 schematic.

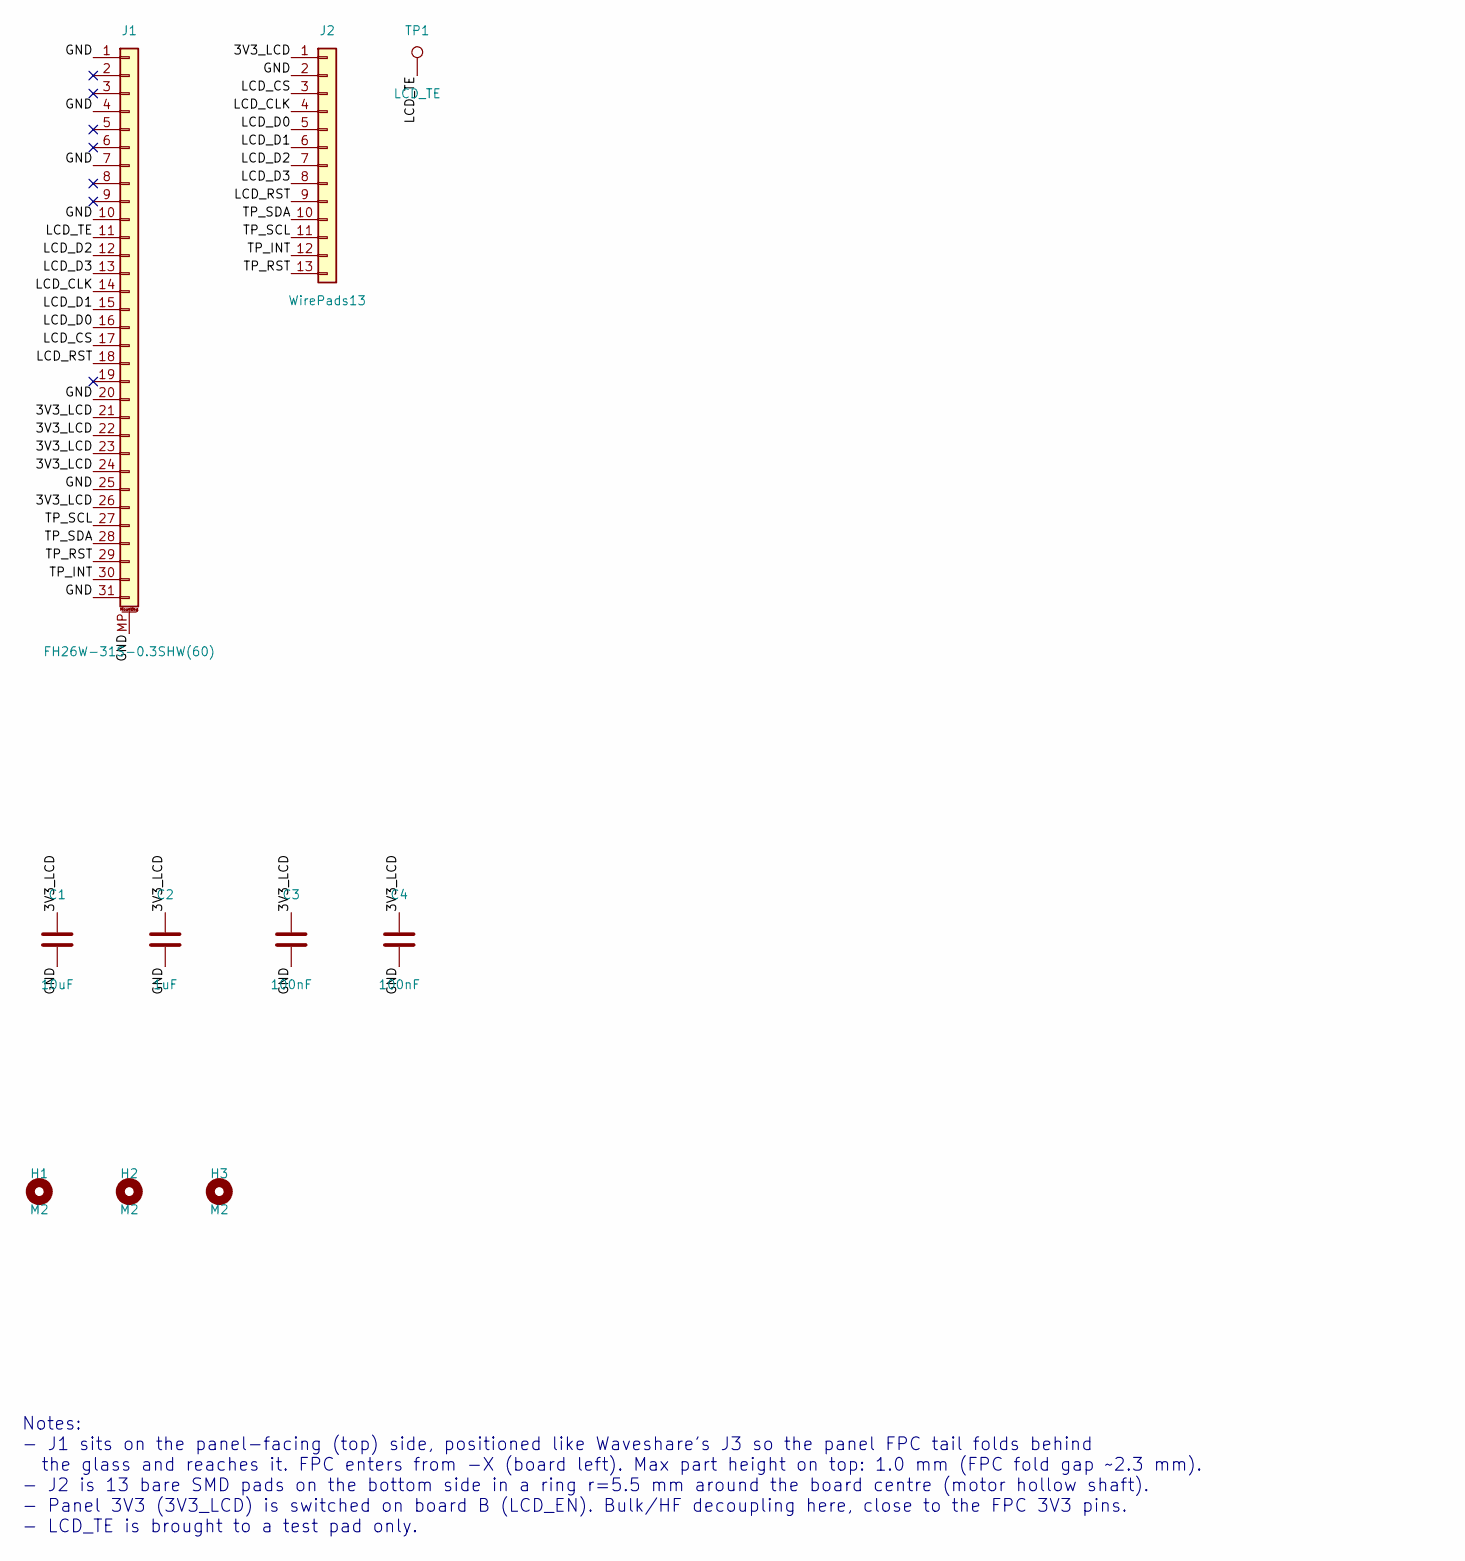
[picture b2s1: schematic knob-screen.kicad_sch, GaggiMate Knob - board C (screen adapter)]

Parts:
C1: 10uF; C_0603_1608Metric; MPN CL10A106KP8NNNC; LCSC C19702
C2: 1uF; C_0402_1005Metric; MPN CL05A105KA5NQNC; LCSC C52923
C3, C4: 100nF; C_0402_1005Metric; MPN CL05B104KO5NNNC; LCSC C1525
H1, H2, H3: M2; MountingHole_2.2mm_M2
J1: FH26W-31S-0.3SHW(60); Hirose_FH26-31S-0.3SHW_2Rows-31Pins-1MP_P0.60mm_Horizontal; MPN FH26W-31S-0.3SHW(60); LCSC C2973806
J2: WirePads13; WirePads_Ring13_R5.5mm
TP1: LCD_TE; TestPoint_Pad_D1.0mm

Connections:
/3V3_LCD: C1.1, C2.1, C3.1, C4.1, J1.21, J1.22, J1.23, J1.24, J1.26, J2.1
/GND: C1.2, C2.2, C3.2, C4.2, J1.1, J1.4, J1.7, J1.10, J1.20, J1.25, J1.31, J1.MP (MountPin), J2.2
/LCD_CLK: J1.14, J2.4
/LCD_CS: J1.17, J2.3
/LCD_D0: J1.16, J2.5
/LCD_D1: J1.15, J2.6
/LCD_D2: J1.12, J2.7
/LCD_D3: J1.13, J2.8
/LCD_RST: J1.18, J2.9
/LCD_TE: J1.11, TP1.1
/TP_INT: J1.30, J2.12
/TP_RST: J1.29, J2.13
/TP_SCL: J1.27, J2.11
/TP_SDA: J1.28, J2.10

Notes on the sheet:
Notes: - J1 sits on the panel-facing (top) side, positioned like Waveshare's J3 so the panel FPC tail folds behind the glass and reaches it. FPC enters from -X (board left). Max part height on top: 1.0 mm (FPC fold gap ~2.3 mm). - J2 is 13 bare SMD pads on the bottom side in a ring r=5.5 mm around 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

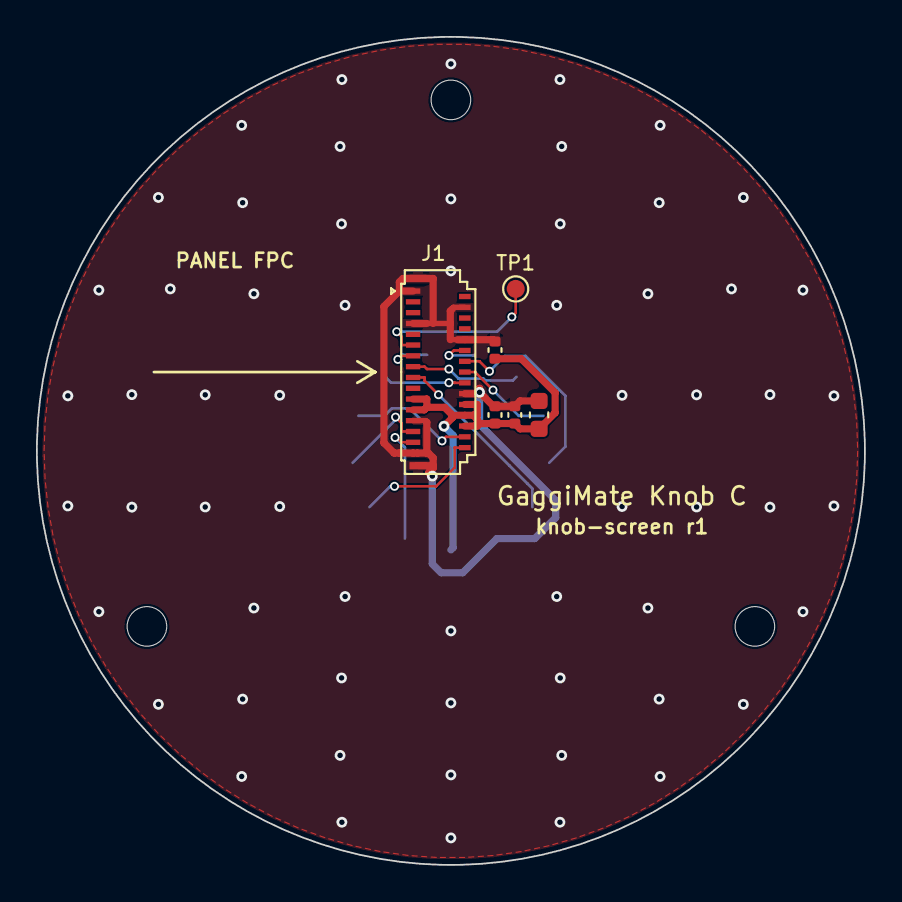
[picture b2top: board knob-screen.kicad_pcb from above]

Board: 2 copper layers, 46.0 x 46.0 mm, 10 parts (1 on the bottom side), 14 nets.

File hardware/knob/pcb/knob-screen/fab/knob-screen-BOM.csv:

Comment,Designator,Footprint,LCSC
10uF,C1,C_0603_1608Metric,C19702
1uF,C2,C_0402_1005Metric,C52923
100nF,"C3,C4",C_0402_1005Metric,C1525
FH26W-31S-0.3SHW(60),J1,Hirose_FH26-31S-0.3SHW_2Rows-31Pins-1MP_P0.60mm_Horizontal,C2973806
